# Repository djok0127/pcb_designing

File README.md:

# pcb_designing
learning about pcb design

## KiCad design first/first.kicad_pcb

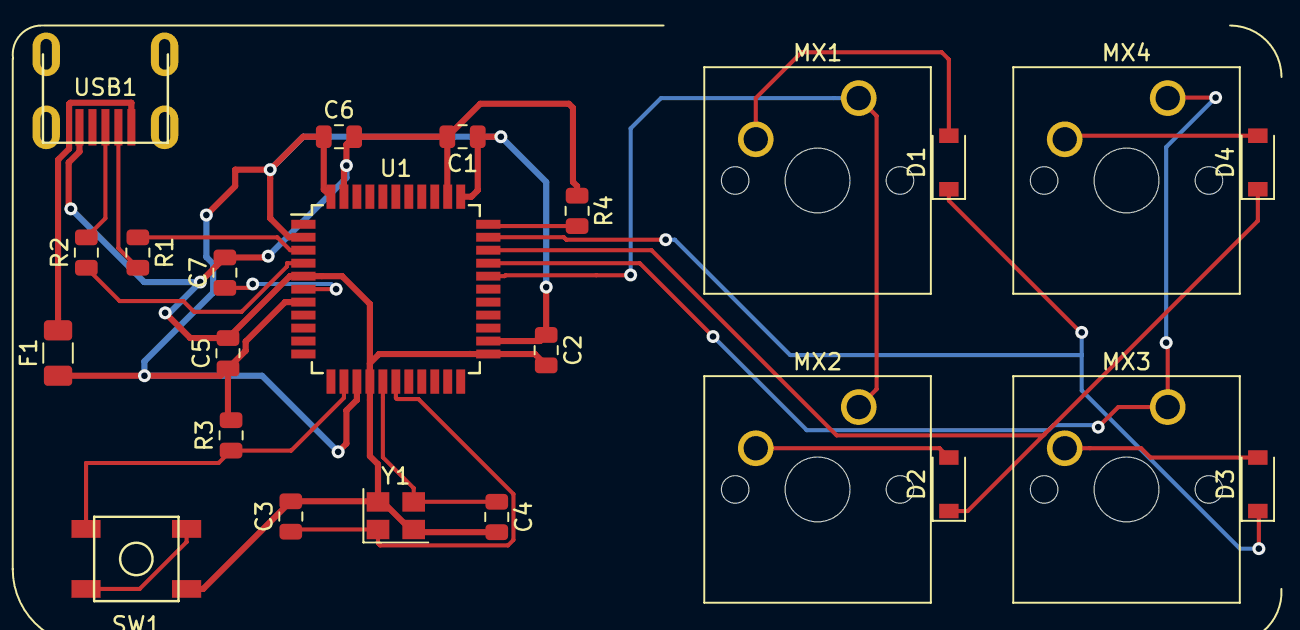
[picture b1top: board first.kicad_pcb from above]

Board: 2 copper layers, 24 parts (0 on the bottom side), 20 nets.

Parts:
C1, C2, C5: 0.1uF; C_0805_2012Metric
C3, C4: 22pF; C_0805_2012Metric
C6: 10uF; C_0805_2012Metric
C7: 1uF; C_0805_2012Metric
D1, D2, D3, D4: SOD-123; D_SOD-123
F1: 500mA; Fuse_1206_3216Metric
MX1, MX2, MX3, MX4: MX-NoLED; SW_Cherry_MX_1.00u_PCB
R1, R2: 22; R_0805_2012Metric
R3, R4: 10k; R_0805_2012Metric
SW1: SW_Push; SKQG-1155865
U1: ATmega32U4-AU; TQFP-44_10x10mm_P0.8mm
USB1: Molex-0548190589
Y1: 16MHz; Crystal_SMD_3225-4Pin_3.2x2.5mm

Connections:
+5V: C1.1, C2.1, C5.1, C6.1, F1.1, R3.2, U1.2, U1.7, U1.14, U1.24, U1.34, U1.44
COL0: MX1.1, MX2.1, U1.29
COL1: MX3.1, MX4.1, U1.30
D+: R2.2, USB1.3
D-: R1.2, USB1.4
GND: C1.2, C2.2, C3.2, C4.2, C5.2, C6.2, C7.2, R4.1, SW1.1, U1.5, U1.15, U1.23, U1.35, U1.43, USB1.1, Y1.2, Y1.4
unnamed: C3.1, U1.17, Y1.1
unnamed: C4.1, U1.16, Y1.3
unnamed: C7.1, U1.6
unnamed: D1.2, MX1.2
unnamed: D2.2, MX2.2
unnamed: D3.2, MX3.2
unnamed: D4.2, MX4.2
unnamed: R1.1, U1.3
unnamed: R2.1, U1.4
unnamed: R3.1, SW1.2, U1.13
unnamed: R4.2, U1.33
ROW0: D1.1, D3.1, U1.32
ROW1: D2.1, D4.1, U1.31
VCC: F1.2, USB1.5

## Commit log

2021-06-06 Add Submodules
2021-06-06 added pretty
2021-07-02 first pcb done
